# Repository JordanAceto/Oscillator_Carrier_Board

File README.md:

# PCB carrier board for VCO plug-in boards.

### This PCB is designed to accomodate various oscillator boards documented elsewhere on my github page. Pots and jacks are mounted on this board, which can be affixed to a Eurorack panel. This way you can have one carrier board/panel, and swap in various VCO designs. 

### A 14hp pcb panel is included in this repo as a cheap panel option.

### Since the panal and panel-mount components are typically a large expense in a synth module, this allows you to evaluate and experiment with different oscillator designs economically.

### Various plug-in boards have already been designed as part of a different project, and this seemed like an easy way to leverage an existing design in order to mess around with a Eurorack setup.

### Here is an example of one of the plug-in boards: [LINK](https://github.com/JordanAceto/CEM3340_VCO "CEM3340 VCO")

Revision | breadboarded | schematic | pcb layout | built and tested | documentation
------|--------------|-----------|------------|------------------|---------------
1       | &#9745; | &#9745; | &#9745; | &#9744; | &#9744;

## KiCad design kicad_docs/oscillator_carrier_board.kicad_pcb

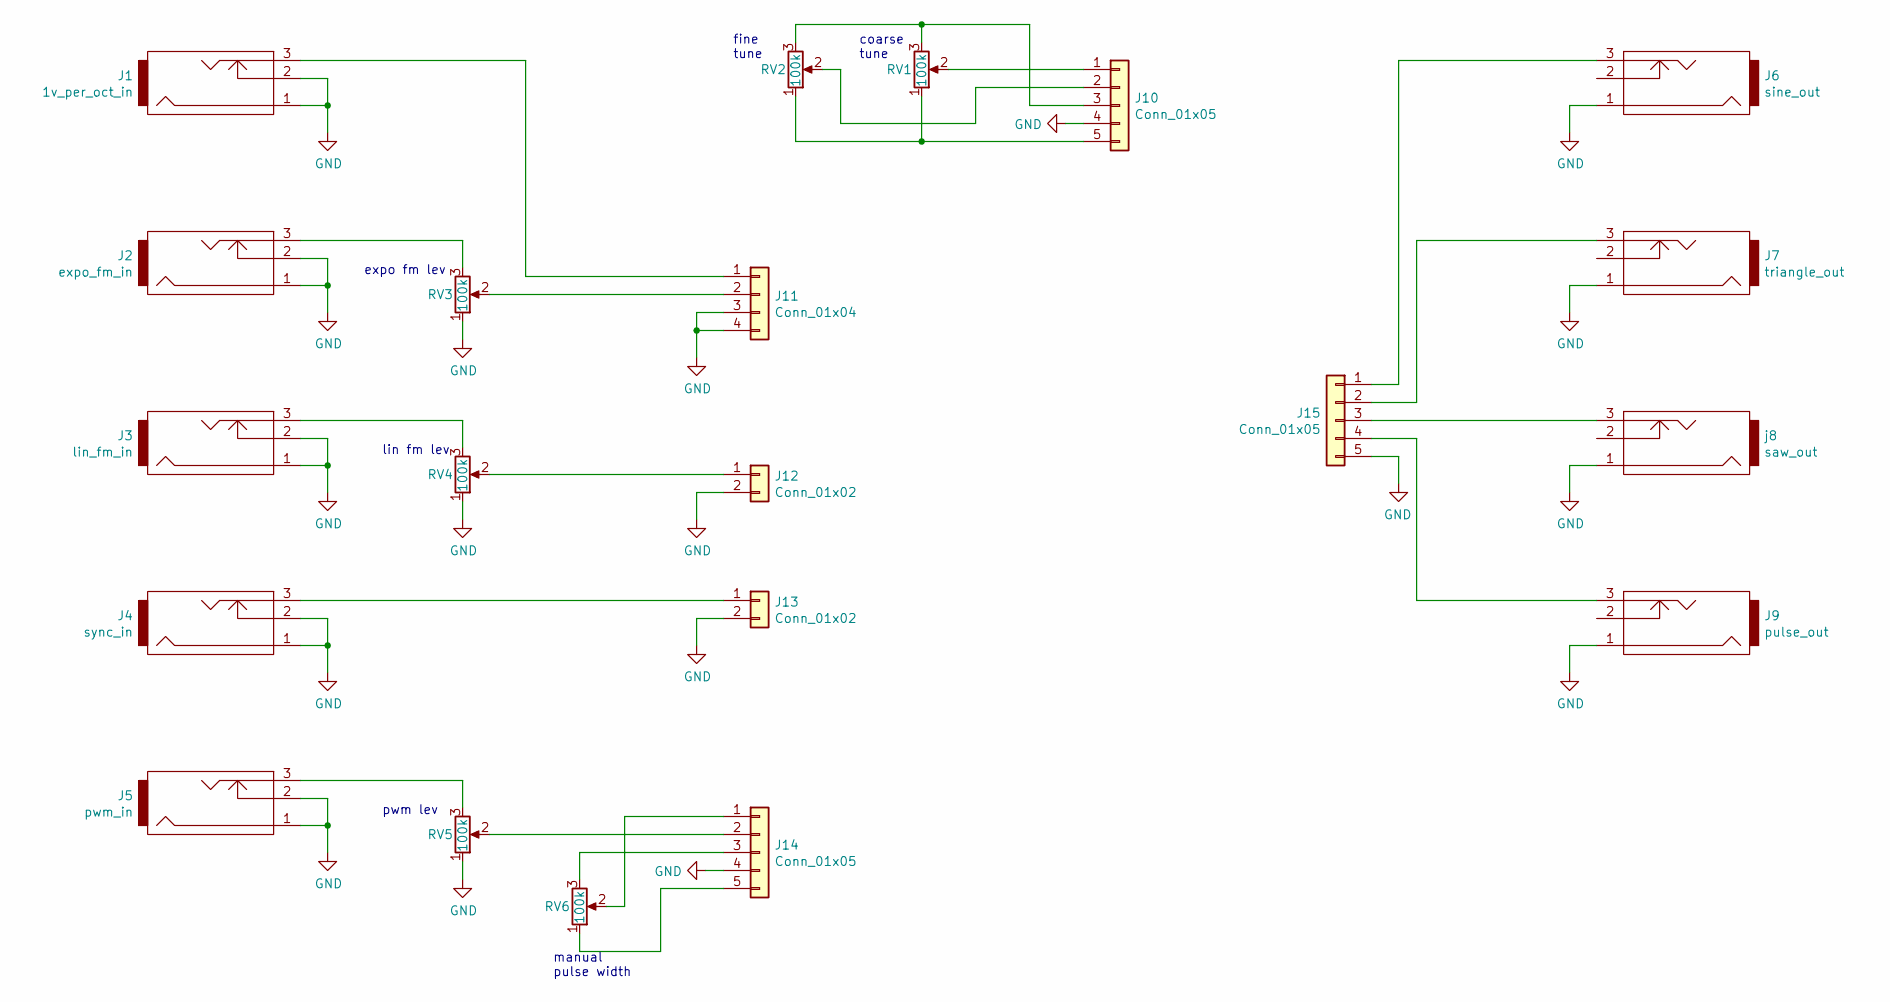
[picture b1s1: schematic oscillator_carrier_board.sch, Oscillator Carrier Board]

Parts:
J1: 1v_per_oct_in; PJ301M-12
J2: expo_fm_in; PJ301M-12
J3: lin_fm_in; PJ301M-12
J4: sync_in; PJ301M-12
J5: pwm_in; PJ301M-12
J6: sine_out; PJ301M-12
J7: triangle_out; PJ301M-12
J9: pulse_out; PJ301M-12
J10, J14, J15: Conn_01x05; PinSocket_1x05_P2.54mm_Vertical
J11: Conn_01x04; PinSocket_1x04_P2.54mm_Vertical
J12, J13: Conn_01x02; PinSocket_1x02_P2.54mm_Vertical
RV1, RV2, RV3, RV4, RV5, RV6: 100k; Potentiometer_Alpha_RD901F-40-00D_Single_Vertical_CircularH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
j8: saw_out; PJ301M-12

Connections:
GND: J1.1, J1.2, J2.1, J2.2, J3.1, J3.2, J4.1, J4.2, J5.1, J5.2, J6.1, J7.1, J9.1, J10.4, J11.3, J11.4, J12.2, J13.2, J14.4, J15.5, RV3.1, RV4.1, RV5.1, j8.1
unnamed: J1.3, J11.1
unnamed: J2.3, RV3.3
unnamed: J3.3, RV4.3
unnamed: J5.3, RV5.3
unnamed: J10.1, RV1.2
unnamed: J10.2, RV2.2
unnamed: J10.3, RV1.3, RV2.3
unnamed: J10.5, RV1.1, RV2.1
unnamed: J11.2, RV3.2
unnamed: J12.1, RV4.2
unnamed: J4.3, J13.1
unnamed: J14.1, RV6.2
unnamed: J14.2, RV5.2
unnamed: J14.3, RV6.3
unnamed: J14.5, RV6.1
unnamed: J6.3, J15.1
unnamed: J7.3, J15.2
unnamed: J15.3, j8.3
unnamed: J9.3, J15.4

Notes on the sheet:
coarse tune
fine tune
expo fm lev
lin fm lev
pwm lev
manual pulse width

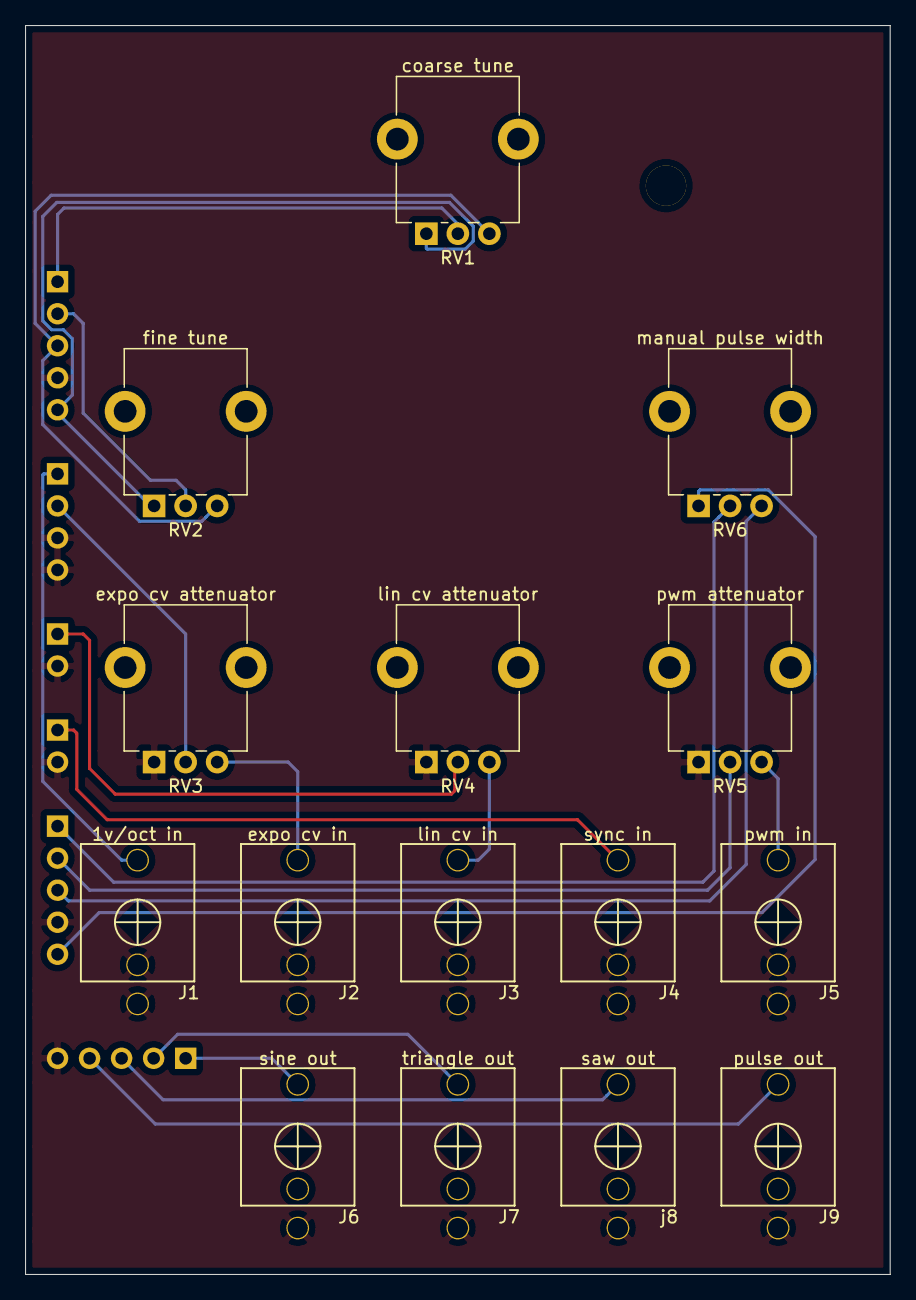
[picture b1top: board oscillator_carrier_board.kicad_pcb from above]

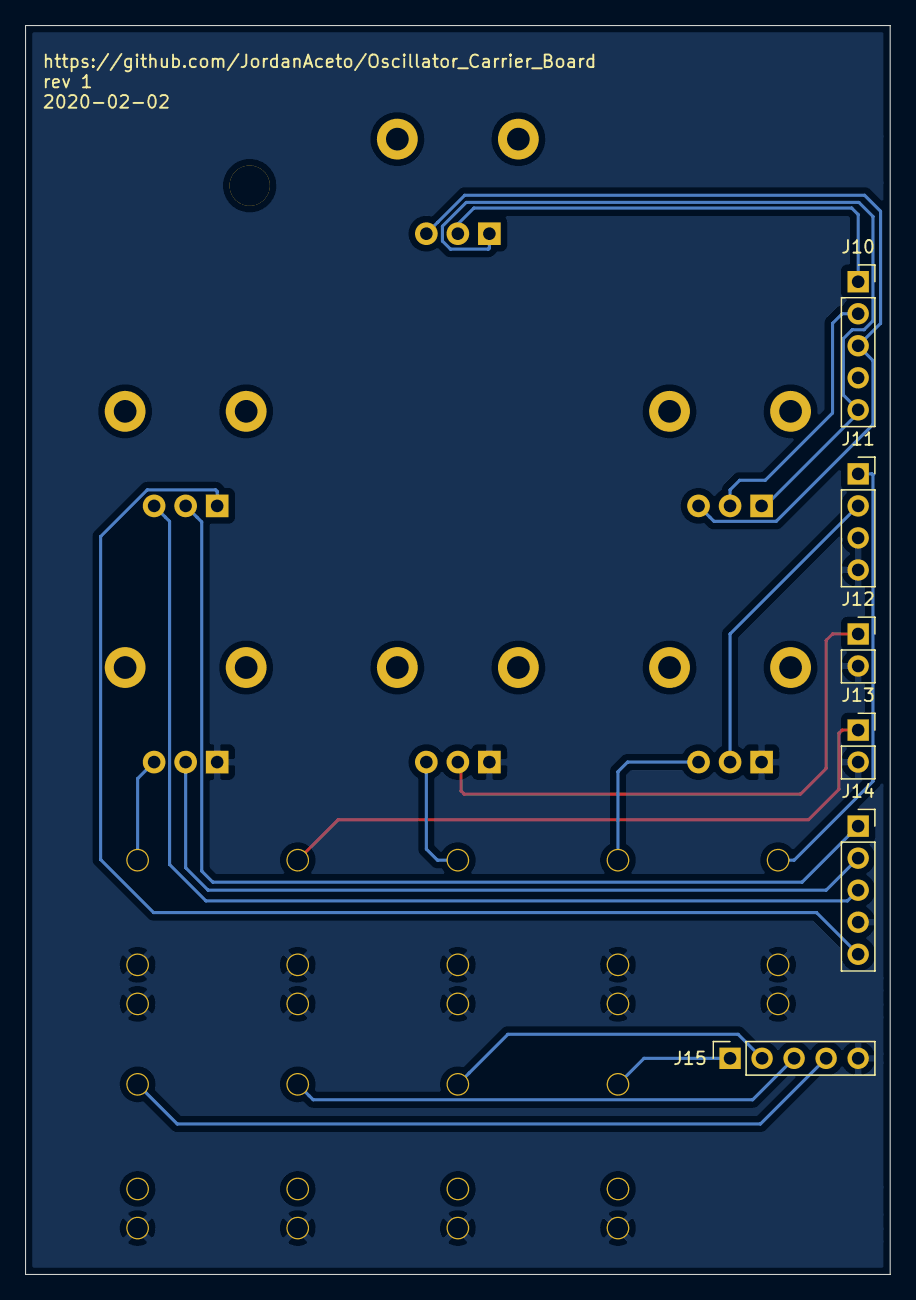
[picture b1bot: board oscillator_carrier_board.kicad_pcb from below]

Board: 2 copper layers, 68.6 x 99.1 mm, 21 parts (6 on the bottom side), 20 nets.

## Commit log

2020-02-02 Create LICENSE
2020-02-02 add pcb pics
2020-02-02 update silkscreen with git info
2020-02-02 add readme
2020-02-02 update readme, fix copy-paste error
2020-02-23 add schematic pdf
2020-08-06 update front panel, update dir structure
2021-05-25 add front panel, reorganize repo

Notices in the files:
kicad_docs/oscillator_carrier_board.kicad_pcb:
License: CC by 4.0
kicad_docs/oscillator_carrier_board.sch:
creativecommons.org/licenses/by/4.0
CC by 4.0
